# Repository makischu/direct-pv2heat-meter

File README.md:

# direct-pv2heat-meter

## the (initial) idea

This project is about an experimental power2heat application. Photovoltaic shall be used to heat water with a resistive heating rod. Directly off-grid, without any inverter, MPPT tracker, or the like. Note that this is known to be a dumb solution in terms of efficiency (e.g. see [1] or [2]). My goal with this project is to collect data to see how bad my solution really is. And another goal is to keep it safe.

**DANGER!** This project deals with dangerous electric power. Do not reproduce except you really know what you are doing!

As there is no regulator involved to match the characteristic of the pv panels and the heater, special care was taken to dimensioning of the parts. At the start of the project I was about to buy a hot-water heat pump, which comes with a heating rod of 1.5kW@230V (equivalents 6,52A or 35,3 Ohm). This one is not required for the intended usage, so I will use it for the project to avoid any extra plumber work. My local photovoltaic dealer offered 375W modules (datasheet names Vmpp=34,6/32,3V and Impp=10,8/8,7A which equivalents Rmpp=3,2/3,7Ohm per module).

[3] proposes a "PV magic water heater formula: Element ohms equal (Vmp/Imp) x 1.40", which translates to a recommondation of 6.8 pv modules in my case. I chose 6. 6 es even, so I can build 2 strings of 3 modules for an alternate usage. Kirchhoff allows us to double the current by simply putting 2 strings in parallel, and power goes with current squared, so I did not want to waste that option too early.

Dividing into 2 strings resulted in another advantage. The maximum input voltage reduced to 3 *41,1V *1,1=135V. This lead me to the idea of using a TL783 as a first stage of my logic power supply, as it allows 125V in-out voltage difference. Unforfunately it was not availabe at the time of ordering and I did not find a 1:1 replacement. I still wanted to power the logic by the pv itself and ensure galvanic isolation, so i designed in an extra intermediate tap in one string. So the maximum input voltage the logic has to deal with is 41,1V *1,1=45V. This is low enough to find an (available) linear regulator for 24V (for relais supply) and a DC DC converter with 3.3V output (for the logic). Furthermore this allows for direct connection to the current metering IC's breakout board SparkX Power Meter - ACS37800 (Qwiic) [4] (<60V). (not a genius idea; see drawbacks below).

See image for the first attempt's overall wiring:

I said I want to keep the usage safe. This includes that power to the heater shall be interruptable. A certain temperature shall not be exceeded. The interruption is realized with FETs. Big ones with screw terminals (for the beginning I did not want to deal with high power on the PCB). As a temperature sensor I want to use the built-on from the hot-water heat pump. The control is not realized yet, but for the pv hardware I realized it as following: A on-command/trigger-signal has to be received every few seconds. If not, the power output will shut down. That should be safe enough for me.

The logic is realized on an ESP32, as it is well-affordable and offers BLE (read: established way of low-power galvanically isolated communication). As counterpart I built a BLE-Wifi-Bridge, also based on an ESP32 (I chose a Firebeetle, so no soldering on this part). That was enough that all the rest (logging, controlling) could be realized in software.

Although it did not work well, I leave the initially planned (and built) system overview here for reference:

<BR/><BR/><BR/>

## the evolution

This chapter is about selected aspects of the (ongoing) development.

### Delivery Issues

Unforfunately the hot water heat pump was not delivered in time (and still isn't at the time of writing. a typical 2022 issue). So I changed the scope of heating: from water to air. Thus I avoid the delivery issue as I have a few dumb (=resisitve) 230V heaters lying around. As they have different wattages a new idea came across: Can I use different permutations to optimize efficiency? Later. First, I have to solve a different problem:

### Logic Supply Issues. Or 3 $\neq$ 1+2. Or: About pv panel mismatch.

The circuit generally works. But under certain conditions I could not turn on the load without the microcontroller going in reset, which turns the load off again by design. It turns out that the logic's supply voltage :purple_square: drops. Why? 

When connecting a load under low light conditions, the string voltage :yellow_square: drops, in this case from ~120 to ~60V. Then it remains stable. That is expected and should *not* cause any issues.

But I made a wrong assumption. I assumed that every panel contributes the same voltage to the string, like batteries. This is what I tried to exploit to ease my logic supply. But as I could see on the scope, the panel's voltages can diverge a lot! Almost down to zero for the panel that is supposed to support the microcontroller.

The source of this effect is mismatch. See [5] for a good introduction to the topic. In addition to inherent panel variation, we draw an extra current from one panel (to supply the logic). This current is only ~30mA (@20V). This sounds negligable in contrast to the load current (in general >1A). But it is not. Why?

Because a pv panel is not (always) a voltage source. It is known to be more like a current source. Well in my opinion it is both, but it depends on the operating point. And for operation points "far left of the MPP" a current source is definitely the better model. See plot.

Let's zoom in to our "current source", plot it for 3 panels, assuming a little variation. As Kirchoff forces the current to be the same for all 3, voltage has to vary *a lot*. 

In the end this effect makes the initially proposed circuit fail in "current source mode", or said otherwise: it only works for high irradiation. 

A possible solution: Characterize the panels, hope that one is significantly better than all others, and hand-select the "best" one for the logic supply. Or make all others worse artifically, by a small extra load. Both approaches do not seem reasonable to me.

A more realistic solution: Generate the required votages from the whole string (3 panels instead of just 1). Unfortunately it is not soo easy to find (linear) regulators or (dc/dc) converters for that (wide) input range. Furthermore we need to consider the similar effect when switching from parallel (2x3 panels) to serial (1x6 panels) configuration. 

### Burnt FET and relay

Although overengineered in terms of voltage and current ability I managed to burn FETs. After some experimentes it was conductive regardless of gate signal. Consequently I burnt the relay, too, as it is not designed to break significant DC current at high voltage. For our purpose FETs shall either block or conduct, nothing in between, to prevent excessive power loss and thus cause its death. I assume I did not care enough about that in my first design.

So I went for a gate driver IC. Most of them offer undervoltage lockout (UVLO), but all that i have seen would suffer from oscillation in my application. UVLO disables the FET when voltage is low, thus removing the load. Removing the load leads to increasing voltage, thus enabling the FET again. For this reason I introduced a latching logic, which causes the FET to remain off in case of UVLO. 

### Server Logic

While I started with almost every logic implemented at a server in (python) software, the external components should not be stricly necessary in the long term. More work shall be done in firmware. 

[Here](theory/datasheettheory.md) I described some theory that might help with devoloping the optimization algorithm.

<BR/><BR/><BR/>

## the (preliminary) final solution

There were further issues I addressed with intermediate experiments (it's not a full diary here). In the end this resulted in a new architecture (where 1 power transistor and 1 relay is sufficient) and several small improvements (robust multi-stage power supply generation for the logic, strong fet driver with latching UVLO, also powerpath integrated on a PCB, thus avoiding external wiring, including voltage+current measurement, reducing external components, ...). 

The new architecture's power path:

Updated system overview:

Although schematics and source code are available in this repository, there is no full bill of material or building instruction. Note that the main unit consists of 2 dependent PCBs. This enabled sequential development and stacking in a din rail housing (an apra rail DB 6).  Here is an impression of the result:

In contrast to the first attempts, the number of wires is greatly reduced. Only 6 power wires are required: 2x2 for the pv input and 2 for the power output (top). I spent another 6 logic ports (bottom), for 1Wire temperature sensor(s) and DigitalIO (not isolated).

## known issues

This is (just) a proof of concept. It works! Hopefully you can extract some ideas. But I do not recommend exact copying, at least not without having read the known issues (which I solved manually for my device but schematics still contain the errors):
- pv2rPower UVLO latch has S and R interchanged. 
- pv2rPower GATE_LOGIC_VCC exceeds 3.3V, as regulator requires minimum load.
- pv2rPower GATE_DRV_OUT level conversion may fail; it limits to ~2V rather than 3.3V.
- pv2rPower LM317s are getting hot. Current consumption should be optimized. Or cooling.
- pv2rLogic L1 was missing in data. I replaced by wire.
- pv2rLogic U2 has wrong footprint. Left not-placed as is not required.
- pv2rLogic 1Wire sometimes fails. Works well with smaller pullup.
- although the pv2heat-meter itself is designed for grid-independence, the server components currently run from grid.
- logic supports my circumstances, may need adaption for your needs (e.g. you could omit the server component and build a truely independent standalone device)
- the optimization algorithm itself is also just a prototype, hardcoded for my (panel) parameters. 
- ...

<BR/>
<BR/>

[1] https://www.solarpaneltalk.com/forum/solar/solar-energy-facts/325254-solar-panel-directly-connected-to-immersion-heater <BR/>
[2] https://diysolarforum.com/threads/direct-solar-pv-water-heater.27937/ <BR/>
[3] http://waterheatertimer.org/Solar-power-curves-for-water-heater.html <BR/>
[4] https://www.sparkfun.com/products/17873 <BR/>
[5] https://www.pveducation.org/pvcdrom/modules-and-arrays/mismatch-for-cells-connected-in-series and https://www.pveducation.org/node/168/talk <BR/>

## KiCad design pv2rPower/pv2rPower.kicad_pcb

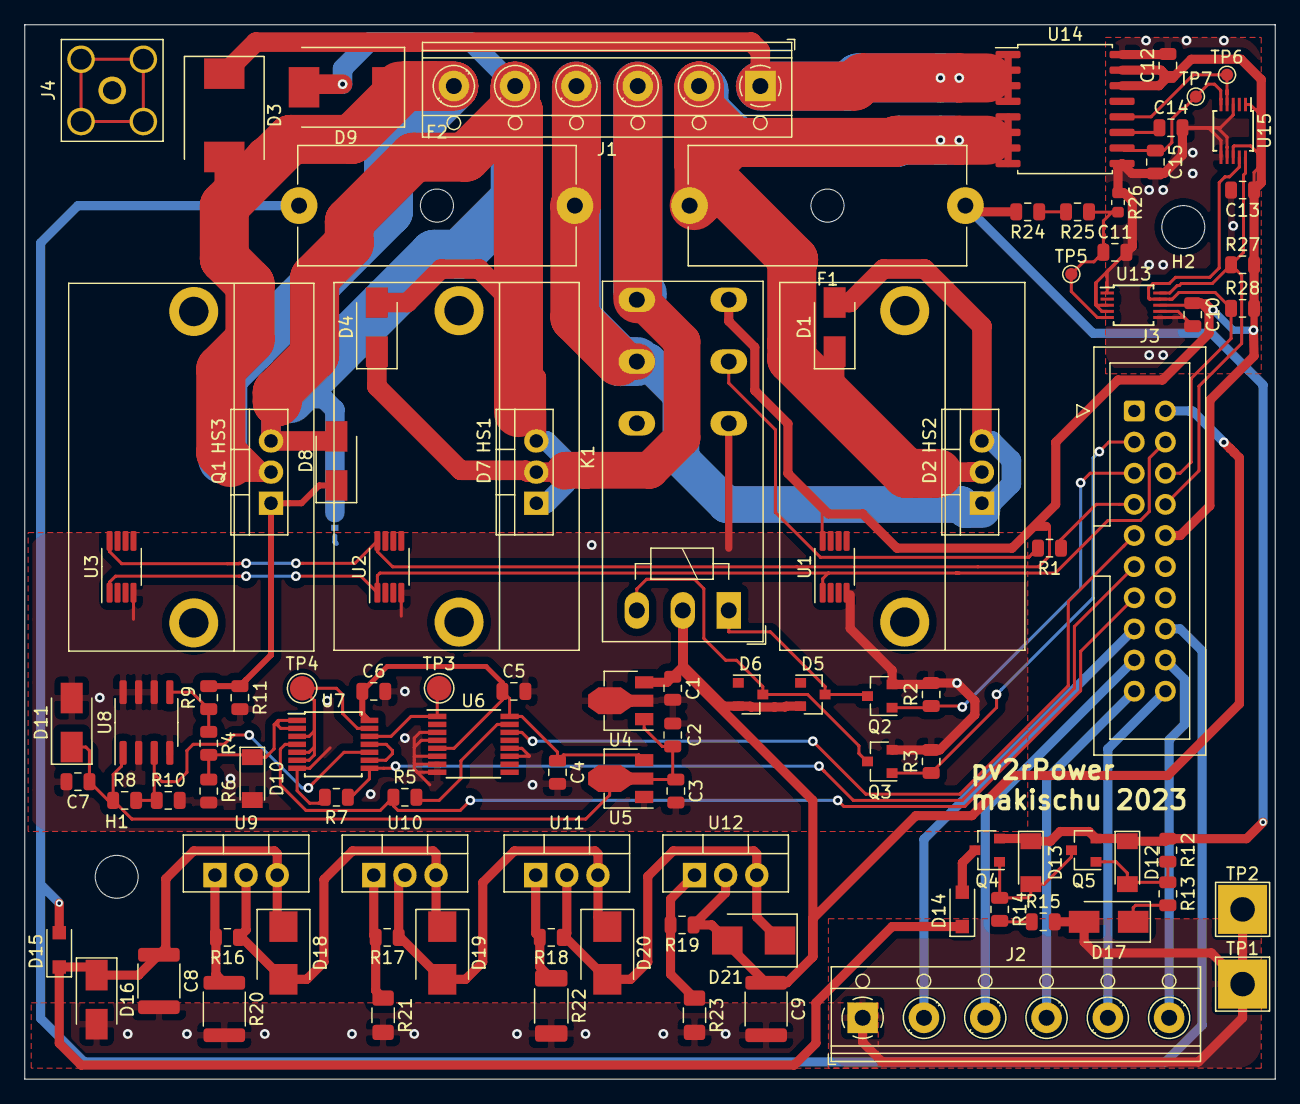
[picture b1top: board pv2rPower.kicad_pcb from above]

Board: 2 copper layers, 102.0 x 86.0 mm, 104 parts (1 on the bottom side), 56 nets.

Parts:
C1: 330n C107132; C_0805_2012Metric
C2, C5, C6, C7, C10, C12, C13: 100n CC0805KRX7R9BB104; C_0805_2012Metric
C3, C4: 10u CL21A106KAYNNNE; C_0805_2012Metric
C8, C9: FS43X105K251EGG; C_1812_4532Metric
C11: 1u CL21B105KBFNNNE; C_0805_2012Metric
C14: 4.7u CL21A475KAQNNNE; C_0805_2012Metric
C15: 1n CL21B102KBCNNNC; C_0805_2012Metric
D1, D4, D16: SMAJ150A; D_SMA
D2, D7: V30200C-E3/4W C500643; TO-220-3_Vertical
D3, D9: SMCJ250A; D_SMC
D5, D6: BAV99,215 C2500; SOT-23
D8, D11: SMAJ15A; D_SMA
D10: ZMM3V3-M; D_MiniMELF
D12, D13: ZMM5V6-M; D_MiniMELF
D14, D15: SM4007PL; D_SOD-123F
D17: 3SMAJ5952B-TP; D_SMA
D18, D19, D20, D21: 1SMB5938BT3G; D_SMB
F1, F2: Fuse; Fuseholder_Cylinder-5x20mm_Schurter_0031_8201_Horizontal_Op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
H1, H2: MountingHole; MountingHole_3.5mm
HS1, HS2, HS3: SK 525 30 ST; Heatsink_Fischer_SK525_30_ST_TO220_2xDrill2.5mm
J1, J2: Screw_Terminal_01x06; TerminalBlock_RND_205-00016_1x06_P5.00mm_Horizontal
J3: C3405; IDC-Header_2x10_P2.54mm_Vertical
J4: Conn_Coaxial; SMA_Amphenol_132203-12_Horizontal
JP1: SolderJumper_2_Bridged; SolderJumper-2_P1.3mm_Bridged_RoundedPad1.0x1.5mm
K1: RT424F24; Relay_DPDT_Schrack-RT2-FormC-Dual-Coil_RM5mm
Q1: IRFB4332PbF C19941; TO-220-3_Vertical
Q2, Q3: 2N7002; SOT-23
Q4, Q5: FTZ30P35G; SOT-23
R1, R5: 1K; R_0805_2012Metric
R2, R3, R4, R6: 100K; R_0805_2012Metric
R7, R11: 100k; R_0805_2012Metric
R8, R10: DNP; R_0805_2012Metric
R9: 10R; R_0805_2012Metric
R12, R13, R14, R15: 220K; R_0805_2012Metric
R16, R17: 680; R_0805_2012Metric
R18: 470; R_0805_2012Metric
R19: 270; R_0805_2012Metric
R20: 62000 CR1812F62K0E04Z; R_1812_4532Metric
R21: 45300 WR12X4532FTL; R_1206_3216Metric
R22: 20k RS-10K2002FT; R_2010_5025Metric
R23: 4870 RS-06K4871FT; R_1206_3216Metric
R24, R25: 1M; R_0805_2012Metric
R26: 6.8k RT0603BRE076K8L; R_0603_1608Metric
R27, R28: DNP 4.7K; R_0805_2012Metric
TP1, TP2: TestPoint_Probe; TestPoint_THTPad_4.0x4.0mm_Drill2.0mm
TP3, TP4: TestPoint; TestPoint_Pad_D2.0mm
TP5, TP6, TP7: TestPoint; TestPoint_Pad_D1.0mm
U1, U3: DNP; MSOP-8_3x3mm_P0.65mm
U2: DS18B20U; MSOP-8_3x3mm_P0.65mm
U4: L78L12_SOT89 C347272; SOT-89-3
U5: HT7533-1 C14289; SOT-89-3
U6: CD4043BPWR; TSSOP-16_4.4x5mm_P0.65mm
U7: CD4093BPWR; TSSOP-14_4.4x5mm_P0.65mm
U8: XJNG2103; SOIC-8_3.9x4.9mm_P1.27mm
U9, U10, U11, U12: LM317K-TA3-T; TO-220-3_Vertical
U13, U15: ADS1115IDGS; TSSOP-10_3x3mm_P0.5mm
U14: ACS710KLATR-12CB-T; SOIC-16W_7.5x10.3mm_P1.27mm

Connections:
1W: J3.4, U1.1, U2.1, U3.1
/pv2rGateDrv/FET_GATE: D8.1, Q1.1, R9.2, R11.1
/pv2rGateDrv/START_ARMED: TP3.1, U6.1, U7.12
/pv2rGateDrv/__DRV_OUT: TP4.1, U7.3, U7.5, U7.6, U7.13
FET_EN: J3.11, R7.1, U7.8
FET_START: J3.9, U6.14
FET_STATUS: J3.13, R5.1, U7.4
GATE_DRV_IN: R8.2, R10.1, U7.10, U8.3
GATE_DRV_OUT: R4.1, R9.1, U8.5
GATE_DRV_VCC: C2.1, C3.1, C7.1, D11.1, R8.1, U4.1, U5.2, U8.1
GATE_LOGIC_VCC: C4.1, C5.1, C6.1, U5.3, U6.5, U6.16, U7.14
GND: C1.2, C2.2, C3.2, C4.2, C5.2, C6.2, C7.2, C8.2, C9.2, C10.2, C11.2, C12.2, C13.2, C14.2, C15.2, D10.2, D11.2, D16.2, D17.2, J2.1, J3.1, J3.12, J3.14, JP1.2, K1.12, Q2.2, Q3.2, R2.2, R3.2, R6.2, R7.2, R10.2, R11.2, R15.2, R20.2, R21.2, R22.2, R23.2, R26.1, TP1.1, TP2.1, U1.4, U2.4, U3.4, U4.2, U5.1, U6.3, U6.4, U6.6, U6.7, U6.8, U6.11, U6.12, U7.7, U8.2, U8.4, U8.6, U8.7, U8.8, U13.1, U13.3, U13.4, U13.6, U13.7, U14.9, U14.16, U15.3, U15.6, U15.7
LOGIC2: J2.2, J3.15
LOGIC3: J2.3, J3.17
LOGIC4: J2.4, J3.19
LOGIC5: J2.5, J3.20
LOGIC6: J2.6, J3.18
unnamed: C11.1, R25.1, R26.2, TP5.1, U13.5
unnamed: C14.1, U14.11
unnamed: C15.1, TP7.1, U14.10, U15.5
unnamed: D5.3, K1.A1, Q2.3
unnamed: D6.3, K1.A2, Q3.3
unnamed: D10.1, R4.2, R6.1, U7.1, U7.2
unnamed: D12.2, Q5.1, R12.2, R13.1
unnamed: D13.2, Q4.1, Q5.3, R14.1
unnamed: D17.1, R13.2
unnamed: D18.2, D19.1, R16.1, U9.2, U10.3
unnamed: D19.2, D20.1, R17.1, U10.2, U11.3
unnamed: D20.2, D21.1, R18.1, U11.2, U12.3
unnamed: K1.11, R1.2
unnamed: R5.2, U6.15
unnamed: R14.2, R15.1
unnamed: R16.2, R20.1, U9.1
unnamed: R17.2, R21.1, U10.1
unnamed: R18.2, R22.1, U11.1
unnamed: R19.2, R23.1, U12.1
unnamed: R24.1, R25.2
unnamed: TP6.1, U14.12, U15.4
unnamed: U7.9, U7.11
PWR_OUT+: D3.1, J1.1, U14.1, U14.2, U14.3, U14.4
PWR_OUT-: D3.2, D9.1, J1.6, Q1.2
R_RESET: J3.5, Q2.1, R2.1
R_SET: J3.3, Q3.1, R3.1
R_STATUS: J3.7, R1.1
S1+: D1.2, D2.1, D2.3, F2.2, J1.4, K1.21
S1+Fused: D15.2, F2.1, J3.16
S1-: D4.2, D7.1, D7.3, D8.2, D9.2, J1.5, JP1.1, Q1.3
S2+: D1.1, D2.2, F1.2, J1.2, U14.5, U14.6, U14.7, U14.8
S2+Fused: D12.1, D13.1, F1.1, Q4.2, Q5.2, R12.1, R24.2
S2+_IfLow: D14.2, Q4.3
S2-: D4.1, D7.2, J1.3, K1.24
S+: C8.1, D14.1, D15.1, D16.1, D18.1, U9.3
SCL: J3.8, R27.1, U13.10, U15.10
SDA: J3.6, R28.1, U13.9, U15.9
V24: C1.1, C9.1, D5.2, D6.2, D21.2, J3.2, K1.A3, R19.1, U4.3, U12.2
V33P: C10.1, C12.1, C13.1, J3.10, K1.14, R27.2, R28.2, U1.8, U2.8, U3.8, U13.8, U14.14, U14.15, U15.1, U15.8

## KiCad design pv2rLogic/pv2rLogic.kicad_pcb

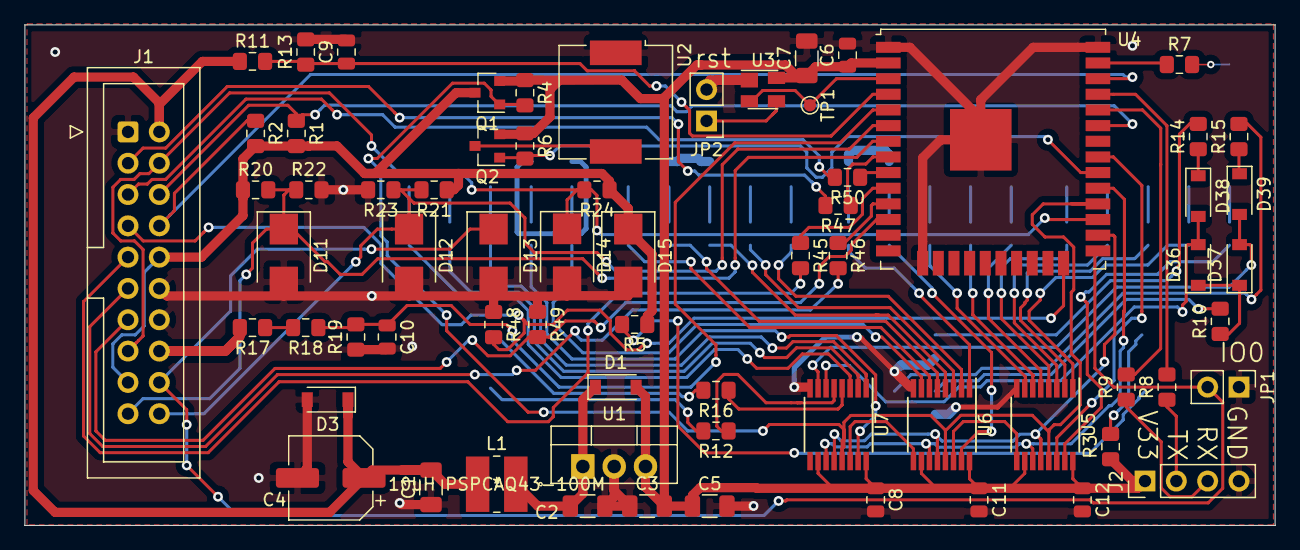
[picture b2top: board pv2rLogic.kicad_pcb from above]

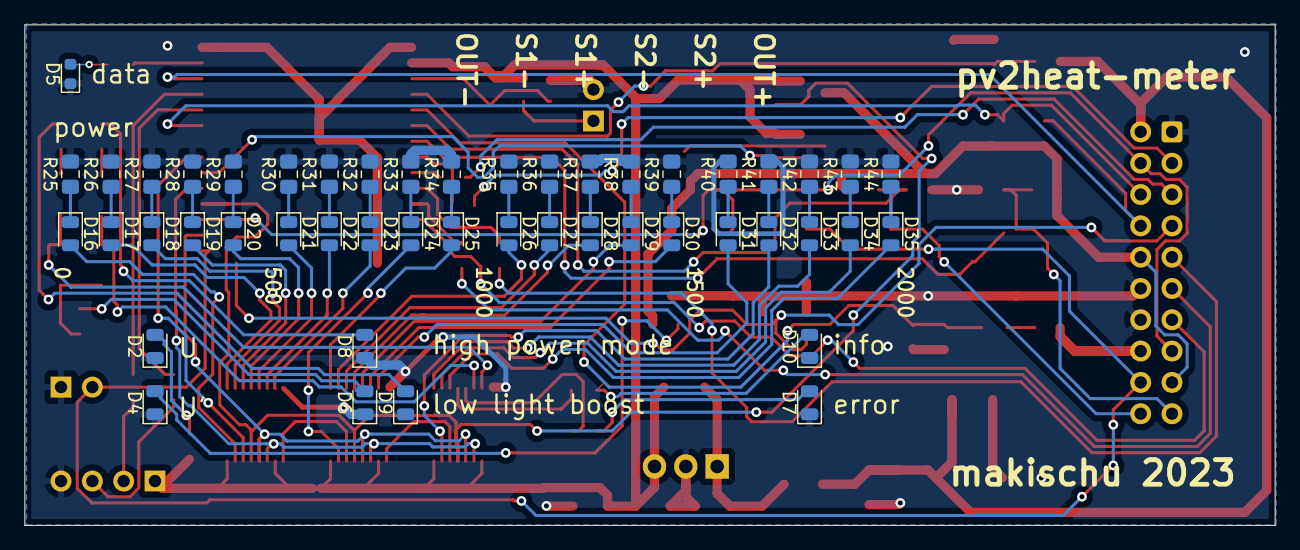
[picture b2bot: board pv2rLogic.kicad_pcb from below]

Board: 2 copper layers, 101.4 x 40.6 mm, 116 parts (48 on the bottom side), 95 nets.

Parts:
C1, C2, C3: 10uF CL31A106KBHNNNE; C_1206_3216Metric
C4: DNP; CP_Elec_6.3x7.7
C5: DNP; C_1206_3216Metric
C6, C8, C9, C10, C11, C12: 0.1uF CC0805KRX7R9BB104; C_0805_2012Metric
C7: 10uF tantal TAJA106K016RNJ; C_1206_3216Metric
D1, D36, D37, D38, D39: 1N4148W; D_SOD-123
D2, D4, D6, D8, D9, D16, D17, D18, D19, D20, D21, D22, D23, D24, D25, D26, D27, D28, D29, D30, D31, D32, D33, D34, D35: LED C2297; LED_0805_2012Metric
D3: BZT52C27; D_SOD-123
D5: LED C72041; LED_0603_1608Metric
D7: LED RD C84256; LED_0805_2012Metric
D10: LED YE C2296; LED_0805_2012Metric
D11, D12, D13, D14, D15: SMLVT3V3; D_SMB
J1: C3405; IDC-Header_2x10_P2.54mm_Vertical
J2: UART; PinHeader_1x04_P2.54mm_Vertical
JP1, JP2: Jumper; PinHeader_1x02_P2.54mm_Vertical
L1: 10uH PSPCAQ43-100M; PSPCAQ43-100M
Q1, Q2: AO3401A; SOT-23
R1, R2, R24: 4.7K; R_0805_2012Metric_Pad1.15x1.40mm_HandSolder
R3, R5, R25, R26, R27, R28, R29, R30, R31, R32, R33, R34, R35, R36, R37, R38, R39, R40, R41, R42, R43, R44: 1K; R_0805_2012Metric_Pad1.15x1.40mm_HandSolder
R4, R6, R48, R49: 100K; R_0805_2012Metric_Pad1.15x1.40mm_HandSolder
R7: 120; R_0805_2012Metric_Pad1.15x1.40mm_HandSolder
R8, R9: 100; R_0805_2012Metric_Pad1.15x1.40mm_HandSolder
R10, R14, R15: 470; R_0805_2012Metric_Pad1.15x1.40mm_HandSolder
R11: 470K; R_0805_2012Metric_Pad1.15x1.40mm_HandSolder
R12, R16, R45, R46, R47, R50: 220; R_0805_2012Metric_Pad1.15x1.40mm_HandSolder
R13, R22, R23: 10K; R_0805_2012Metric_Pad1.15x1.40mm_HandSolder
R17, R18: 1Meg; R_0805_2012Metric_Pad1.15x1.40mm_HandSolder
R19: 13.3k TR0805C13K3P0515; R_0805_2012Metric_Pad1.15x1.40mm_HandSolder
R20, R21: 24K; R_0805_2012Metric_Pad1.15x1.40mm_HandSolder
TP1: EN; TestPoint_Pad_D1.0mm
U1: LCB78_03-0.5; TO-220-3_Vertical
U2: GSD128065YB-3V2400; Buzzer_GSD128065YB
U3: MAX811SEUS-T; SOT-143
U4: ESP32-WROOM-32UE-N8; ESP32-WROOM-32U
U5, U6, U7: SN74HC595PWR; TSSOP-16_4.4x5mm_P0.65mm

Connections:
1W: D14.1, J1.4, J1.15, R24.2, U4.27
DIGIN1: D11.1, J1.19, R20.2, R22.1, U4.7
DIGIN2: D12.1, J1.20, R21.2, R23.1, U4.6
DIGIN3: D13.1, J1.18, JP1.2, U4.25
EN: TP1.1, U3.2, U4.3
FET_EN: J1.11, R46.2
FET_START: J1.9, R45.2
FET_STATUS: J1.13, R49.2, U4.12
GND: C1.1, C2.1, C3.1, C4.2, C5.2, C6.2, C7.2, C8.2, C9.2, C10.2, C11.2, C12.2, D2.1, D3.2, D4.1, D5.1, D6.1, D7.1, D8.1, D9.1, D10.1, D11.2, D12.2, D13.2, D14.2, D15.2, J1.1, J1.12, J1.14, J2.4, JP1.1, JP2.2, R13.2, R19.1, R22.2, R23.2, R25.2, R26.2, R27.2, R28.2, R29.2, R30.2, R31.2, R32.2, R33.2, R34.2, R35.2, R36.2, R37.2, R38.2, R39.2, R40.2, R41.2, R42.2, R43.2, R44.2, R48.1, R49.1, U1.2, U2.1, U3.1, U4.1, U4.15, U4.38, U4.39, U5.8, U6.8, U7.8
IO2: J1.7, R48.2, U4.24
IO4: U4.26, U5.12, U6.12, U7.12
IO5: U4.29, U5.11, U6.11, U7.11
IO18: Q2.1, R6.2, U4.30
IO19: U4.31, U5.14
IO23: R7.1, U4.37
IO25: R45.1, U4.10
IO26: R46.1, U4.11
IO32: R47.1, U4.8
IO33: R50.1, U4.9
IO_PER_EN: Q1.1, R4.2, U4.28, U5.13, U6.13, U7.13
LEDO1: D16.2, U5.15
LEDO2: D17.2, U5.1
LEDO3: D18.2, U5.2
LEDO4: D19.2, U5.3
LEDO5: D20.2, U5.4
LEDO6: D21.2, U5.5
LEDO7: D22.2, U5.6
LEDO8: D23.2, U5.7
LEDO9: D24.2, U6.15
LEDOA: D25.2, U6.1
LEDOB: D26.2, U6.2
LEDOC: D27.2, U6.3
LEDOD: D28.2, U6.4
LEDOE: D29.2, U6.5
LEDOF: D30.2, U6.6
LEDOG: D31.2, U6.7
LEDOH: D32.2, U7.15
LEDOI: D33.2, U7.1
LEDOJ: D34.2, U7.2
LEDOK: D35.2, U7.3
LEDOW: R16.1, U7.4
LEDOX: R12.1, U7.5
LEDOY: D36.2, D38.2, U7.6
LEDOZ: D37.2, D39.2, U7.7
LOGIC3: D15.1, J1.10, J1.17, Q1.3, R1.2, R2.2, R5.1, R20.1, R21.1, R24.1
unnamed: C2.2, D1.1, L1.1, U1.1
unnamed: C9.1, R11.2, R13.1, U4.4
unnamed: C10.1, R18.1, R19.2, U4.5
unnamed: D2.2, R3.2
unnamed: D4.2, R5.2
unnamed: D5.2, R7.2
unnamed: D6.2, R10.2
unnamed: D7.2, R12.2
unnamed: D8.2, R14.2
unnamed: D9.2, R15.2
unnamed: D10.2, R16.2
unnamed: D16.1, R25.1
unnamed: D17.1, R26.1
unnamed: D18.1, R27.1
unnamed: D19.1, R28.1
unnamed: D20.1, R29.1
unnamed: D21.1, R30.1
unnamed: D22.1, R31.1
unnamed: D23.1, R32.1
unnamed: D24.1, R33.1
unnamed: D25.1, R34.1
unnamed: D26.1, R35.1
unnamed: D27.1, R36.1
unnamed: D28.1, R37.1
unnamed: D29.1, R38.1
unnamed: D30.1, R39.1
unnamed: D31.1, R40.1
unnamed: D32.1, R41.1
unnamed: D33.1, R42.1
unnamed: D34.1, R43.1
unnamed: D35.1, R44.1
unnamed: D36.1, D37.1, R10.1
unnamed: D38.1, R14.1
unnamed: D39.1, R15.1
unnamed: J2.2, R8.1
unnamed: J2.3, R9.1
unnamed: JP2.1, U3.3
unnamed: Q2.3, U2.2
unnamed: R8.2, U4.35
unnamed: R9.2, U4.34
unnamed: R17.1, R18.2
unnamed: U5.9, U6.14
unnamed: U6.9, U7.14
R_RESET: J1.5, R50.2
R_SET: J1.3, R47.2
S1+Fused: J1.16, R17.2
SCL: J1.8, R2.1, U4.36
SDA: J1.6, R1.1, U4.33
V24: C1.2, C4.1, D3.1, J1.2, L1.2, R11.1
V33: C3.2, C5.1, C6.1, C7.1, C8.1, C11.1, C12.1, D1.2, J2.1, Q1.2, Q2.2, R3.1, R4.1, R6.1, U1.3, U3.4, U4.2, U5.10, U5.16, U6.10, U6.16, U7.10, U7.16

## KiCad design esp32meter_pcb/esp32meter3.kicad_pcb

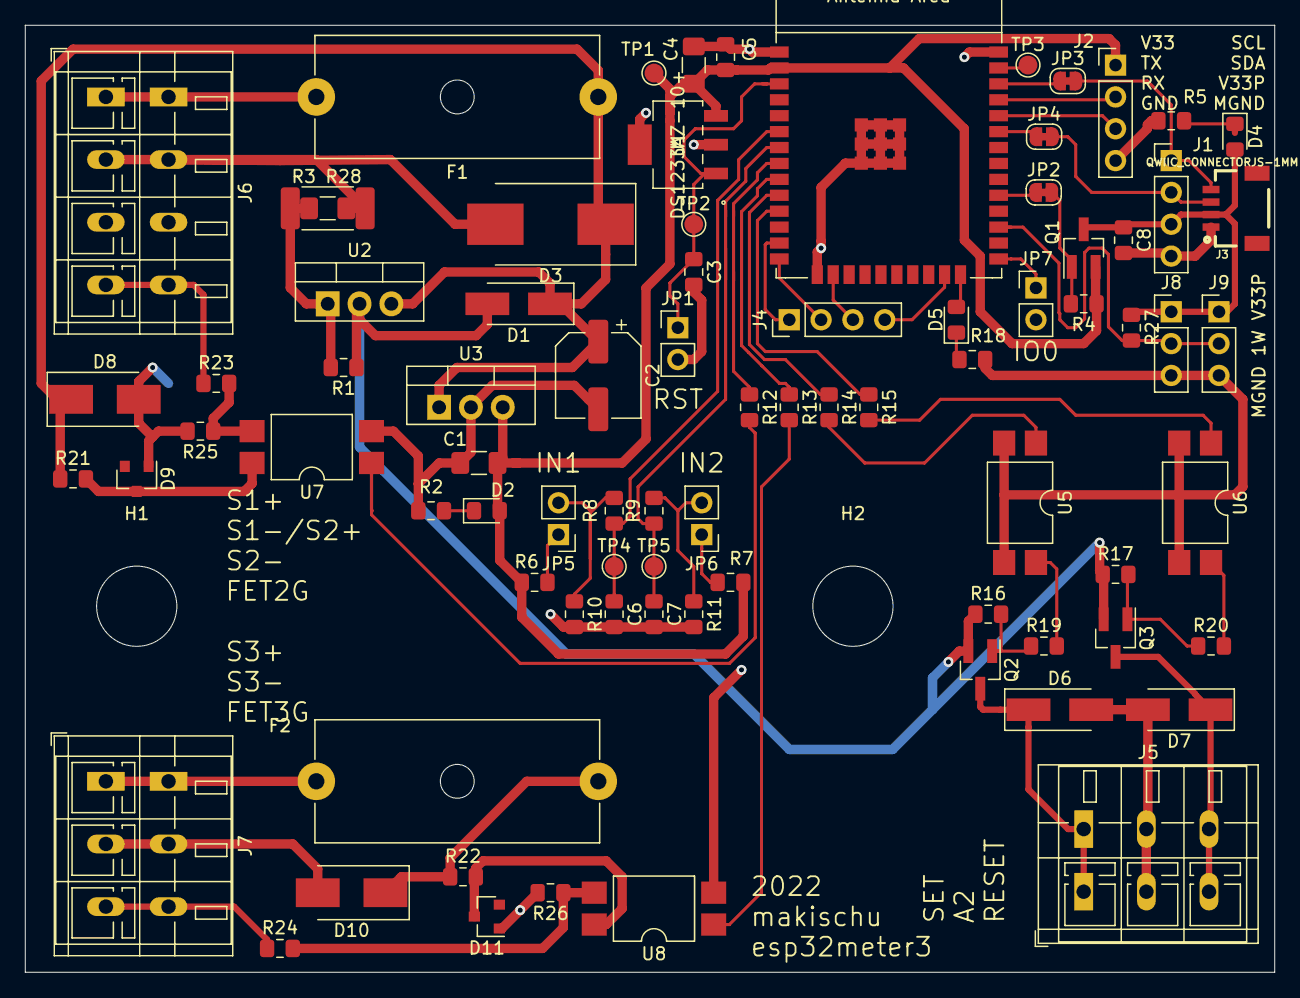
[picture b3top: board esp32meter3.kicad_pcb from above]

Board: 4 copper layers, 99.7 x 75.6 mm, 83 parts (0 on the bottom side), 57 nets.

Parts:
C1, C4: TAJA106K016RNJ; C_1206_3216Metric_Pad1.42x1.75mm_HandSolder
C2: VEJ100M2ATR-0607; CP_Elec_6.3x7.7
C3: 0.01uF; C_0805_2012Metric_Pad1.15x1.40mm_HandSolder
C5: 0.1uF; C_0805_2012Metric_Pad1.15x1.40mm_HandSolder
C6, C7: 0.1u; C_0805_2012Metric_Pad1.15x1.40mm_HandSolder
C8: 0.1uF_DNP; C_0805_2012Metric_Pad1.15x1.40mm_HandSolder
D1, D6, D7: M7; D_SMA_Handsoldering
D2, D4, D5: LED; LED_0805_2012Metric_Pad1.15x1.40mm_HandSolder
D3: SMCJ51A; D_SMC_Handsoldering
D8, D10: 1SMB5953BT3G; D_SMB_Handsoldering
D9, D11: BZX84-C24,215; D_SOT-23_ANK
F1, F2: Fuse; Fuseholder_Cylinder-5x20mm_Schurter_0031_8201_Horizontal_Op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
H1, H2: MountingHole; MountingHole_6.4mm_M6
J1: I2C_DNP; PinHeader_1x04_P2.54mm_Vertical
J2: UART; PinHeader_1x04_P2.54mm_Vertical
J3: QWIIC_CONNECTORJS-1MM; 1X04_1MM_RA
J4: JTAG; PinHeader_1x04_P2.54mm_Vertical
J5, J7: Screw_Terminal_01x03; TerminalBlock_WAGO_236-403_1x03_P5.00mm_45Degree
J6: Screw_Terminal_01x04; TerminalBlock_WAGO_236-404_1x04_P5.00mm_45Degree
J8, J9: OneWire; PinHeader_1x03_P2.54mm_Vertical
JP1, JP5, JP6, JP7: Jumper; PinHeader_1x02_P2.54mm_Vertical
JP2, JP3, JP4: SolderJumper_2_Bridged; SolderJumper-2_P1.3mm_Bridged_RoundedPad1.0x1.5mm
Q1, Q2, Q3: AO3401A; SOT-23_Handsoldering
R1: 274; R_0805_2012Metric_Pad1.15x1.40mm_HandSolder
R2, R5, R12, R13, R14, R15, R18: 220; R_0805_2012Metric_Pad1.15x1.40mm_HandSolder
R3: 4.87K; R_2512_6332Metric_Pad1.52x3.35mm_HandSolder
R4, R8, R9, R10, R11, R25, R26: 100K; R_0805_2012Metric_Pad1.15x1.40mm_HandSolder
R6, R7, R23, R24: 1K; R_0805_2012Metric_Pad1.15x1.40mm_HandSolder
R16, R17: 10K; R_0805_2012Metric_Pad1.15x1.40mm_HandSolder
R19, R20: 22K; R_0805_2012Metric_Pad1.15x1.40mm_HandSolder
R21, R22: 100K 1/8W 0805W8F1003T5E; R_0805_2012Metric_Pad1.15x1.40mm_HandSolder
R27: 4.7K; R_0805_2012Metric_Pad1.15x1.40mm_HandSolder
R28: DNP_4.87K; R_1206_3216Metric_Pad1.42x1.75mm_HandSolder
TP1, TP3, TP4, TP5: TestPoint; TestPoint_Pad_D1.5mm
TP2: EN; TestPoint_Pad_D1.5mm
U1: DS1233AZ-10+; 21-0264_K3+1_MXM
U2: LM338; TO-220-3_Vertical
U3: LCB78_03-0.5; TO-220-3_Vertical
U4: ESP32-WROOM; ESP32-WROOM-32E
U5, U6, U7, U8: BPC-817S; SMDIP-4_W9.53mm

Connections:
/TCK: J4.3, U4.16
/TDI: J4.2, U4.14
/TDO: J4.4, U4.23
/TMS: J4.1, U4.13
EN: C3.1, JP1.1, TP2.1, U1.1, U4.3
FET2G: J6.4, R23.1
FET3G: J7.3, R24.1
IO5_PER_EN: JP2.1, U4.29
IO16_1WIRE: J8.2, J9.2, R27.2, U4.27
IO21_SDA: JP4.1, U4.33
IO22_SCL: JP3.1, U4.36
IO23_SDA2: TP3.1, U4.37
MGND: C1.2, C2.2, C3.2, C4.2, C5.2, C6.2, C7.2, C8.2, D3.2, D6.2, D7.2, J1.4, J2.4, J3.1, J5.2, J6.2, J8.3, J9.3, JP1.2, JP7.2, R2.2, R3.2, R5.2, R10.2, R11.2, R18.2, R28.2, U1.2, U1.4, U3.2, U4.1, U4.15, U4.38, U4.39, U5.2, U5.3, U6.2, U6.3, U7.2, U8.2
unnamed: C6.1, R8.2, TP4.1, U4.6
unnamed: C7.1, R9.1, TP5.1, U4.7
unnamed: D2.1, R2.1
unnamed: D4.1, R5.1
unnamed: D5.1, R18.1
unnamed: D5.2, U4.24
unnamed: J2.2, U4.35
unnamed: J2.3, U4.34
unnamed: JP2.2, Q1.1, R4.2
unnamed: JP5.1, R6.2
unnamed: JP5.2, R8.1, R10.1
unnamed: JP6.1, R7.2
unnamed: JP6.2, R9.2, R11.1
unnamed: JP7.1, U4.25
unnamed: Q2.1, R16.2, R19.1
unnamed: Q3.1, R17.2, R20.1
unnamed: R1.2, R3.1, R28.1, U2.1
unnamed: R12.1, U4.8
unnamed: R13.1, U4.9
unnamed: R14.1, U4.10
unnamed: R15.1, U4.11
unnamed: R19.2, U5.4
unnamed: R20.2, U6.4
unnamed: R23.2, R25.1, U7.3
unnamed: R24.2, R26.1, U8.3
OC1A: R12.2, U7.1
OC2A: R13.2, U8.1
OC3A: R14.2, U5.1
OC4A: R15.2, U6.1
RESET: D7.1, J5.3, Q3.3
S1+: F1.2, J6.1
S2-: D8.2, D9.2, J6.3, R25.2
S3+: F2.2, J7.1
S3-: D10.2, D11.2, J7.2, R26.2
SCL: J1.1, J3.4, JP3.2
SDA: J1.2, J3.3, JP4.2
SET: D6.1, J5.1, Q2.3
V1+: C2.1, D1.1, D3.1, D8.1, F1.1, R21.1, U2.3, U3.1
V1+24: D9.1, R21.2, U7.4
V3+: D10.1, F2.1, R22.1
V3+24: D11.1, R22.2, U8.4
V24: D1.2, Q2.2, Q3.2, R1.1, R16.1, R17.1, U2.2
V33: C1.1, C4.1, C5.1, D2.2, J2.1, Q1.2, R4.1, R6.1, R7.1, TP1.1, U1.3, U3.3, U4.2
V33_PER: C8.1, D4.2, J1.3, J3.2, J8.1, J9.1, Q1.3, R27.1

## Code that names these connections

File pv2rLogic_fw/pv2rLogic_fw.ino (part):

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#define __PER_EN      (17)
#define __BUZZER      (18) // not placed.
#define LED_DATA      (23)
#define DIGIN1        (35)
#define DIGIN2        (34)
#define DIGIN3         (0)  
#define FET_STATUS    (27)
#define R_STATUS       (2)
#define FET_START     (25)
#define FET_EN        (26)
#define R_SET         (32)
#define R_RESET       (33)
#define ONE_WIRE_BUS  (16)
#define ANALOG_PIN24  (36)
#define ANALOG_PINS1  (39)
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  pinMode(dataPin, OUTPUT);   digitalWrite(dataPin,  LOW); 
  pinMode(__BUZZER, OUTPUT);  digitalWrite(__BUZZER, HIGH); 
  pinMode(LED_DATA, OUTPUT);  digitalWrite(LED_DATA, LOW); 
  pinMode(R_SET, OUTPUT);     digitalWrite(R_SET, LOW);
  pinMode(R_RESET, OUTPUT);   digitalWrite(R_RESET, LOW); 
  pinMode(FET_EN, OUTPUT);    digitalWrite(FET_EN, LOW); 
  pinMode(FET_START, OUTPUT); digitalWrite(FET_START, LOW);
 
  pinMode(DIGIN1, INPUT);
  pinMode(DIGIN2, INPUT);
  pinMode(DIGIN3, INPUT);
  pinMode(R_STATUS, INPUT); 
  pinMode(FET_STATUS, INPUT); 

  Serial.begin(115200);
  Serial.print("getXtalFrequencyMhz: ");  Serial.println(getXtalFrequencyMhz());
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  analogSetPinAttenuation(ANALOG_PIN24, ADC_0db);
  adcAttachPin(ANALOG_PINS1);
  analogSetPinAttenuation(ANALOG_PINS1, ADC_0db);
  adcAttachPin(DIGIN1);
  analogSetPinAttenuation(DIGIN1, ADC_11db);
  adcAttachPin(DIGIN2);
  analogSetPinAttenuation(DIGIN2, ADC_11db);
  delay(10);
  digIn1 = readDigIn1();

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
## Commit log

2022-08-05 annotated wiring image
2022-08-12 added my math theory on IV characteristic
2022-08-12 fixed formulas to be visible in github
2022-08-12 added theoretical efficiency calculations
2022-08-12 added theory on efficiency - fixed view
2022-09-25 improved stability, added watchdog and status leds
2022-10-15 explained some issues
2023-04-16 Continued story to working prototype.
2023-04-16 Continued story to working prototype
2023-05-30 added energy counter script
2023-07-14 explained and implemented switching algorithm
    and made bridge and translator more robust
2023-08-18 eliminated current measurement from decision logic

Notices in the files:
pv2rLogic_fw/pv2rLogic_fw.ino:
This example code is in the public domain.
parts and their libraries:
Copyright 2021 Accelerated Designs. All rights reserved.
